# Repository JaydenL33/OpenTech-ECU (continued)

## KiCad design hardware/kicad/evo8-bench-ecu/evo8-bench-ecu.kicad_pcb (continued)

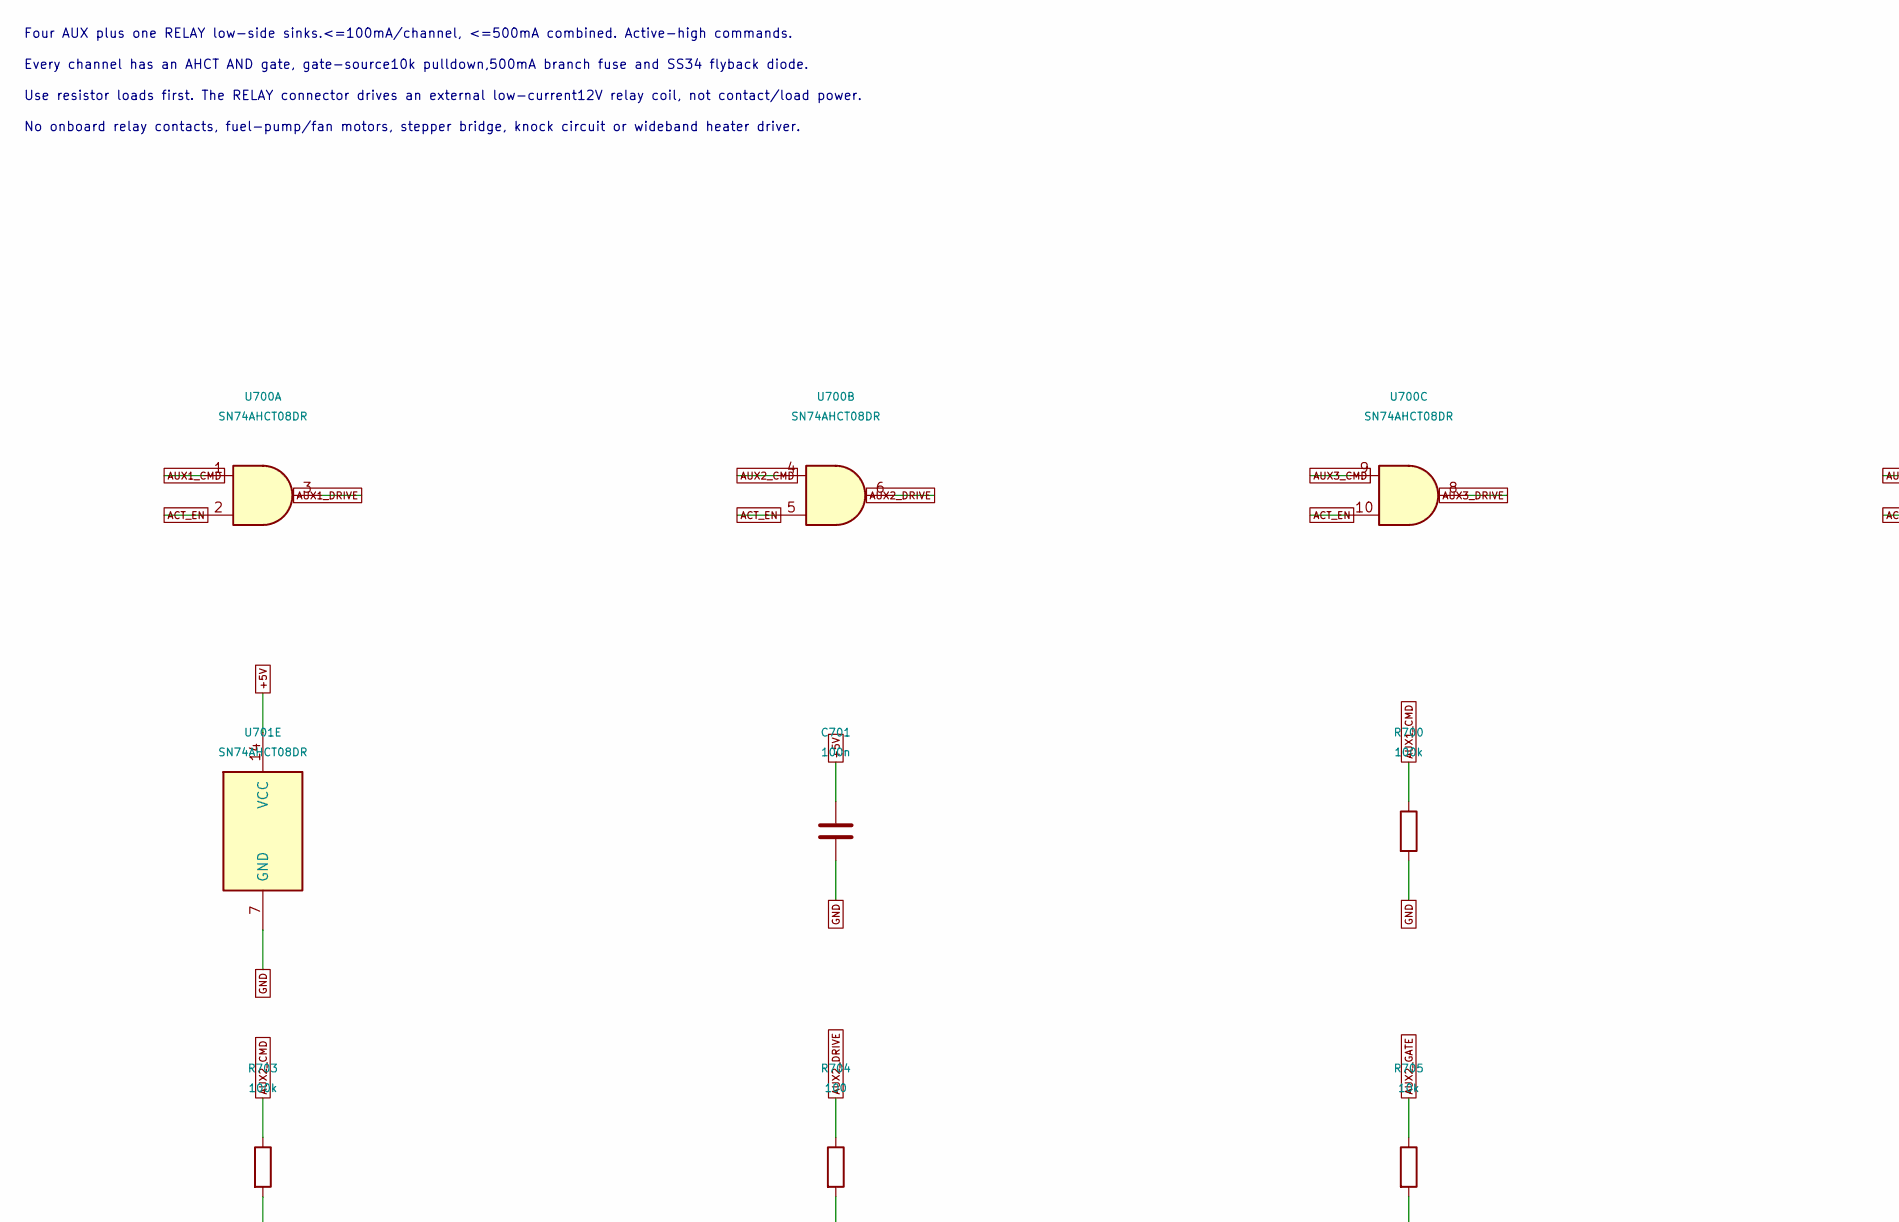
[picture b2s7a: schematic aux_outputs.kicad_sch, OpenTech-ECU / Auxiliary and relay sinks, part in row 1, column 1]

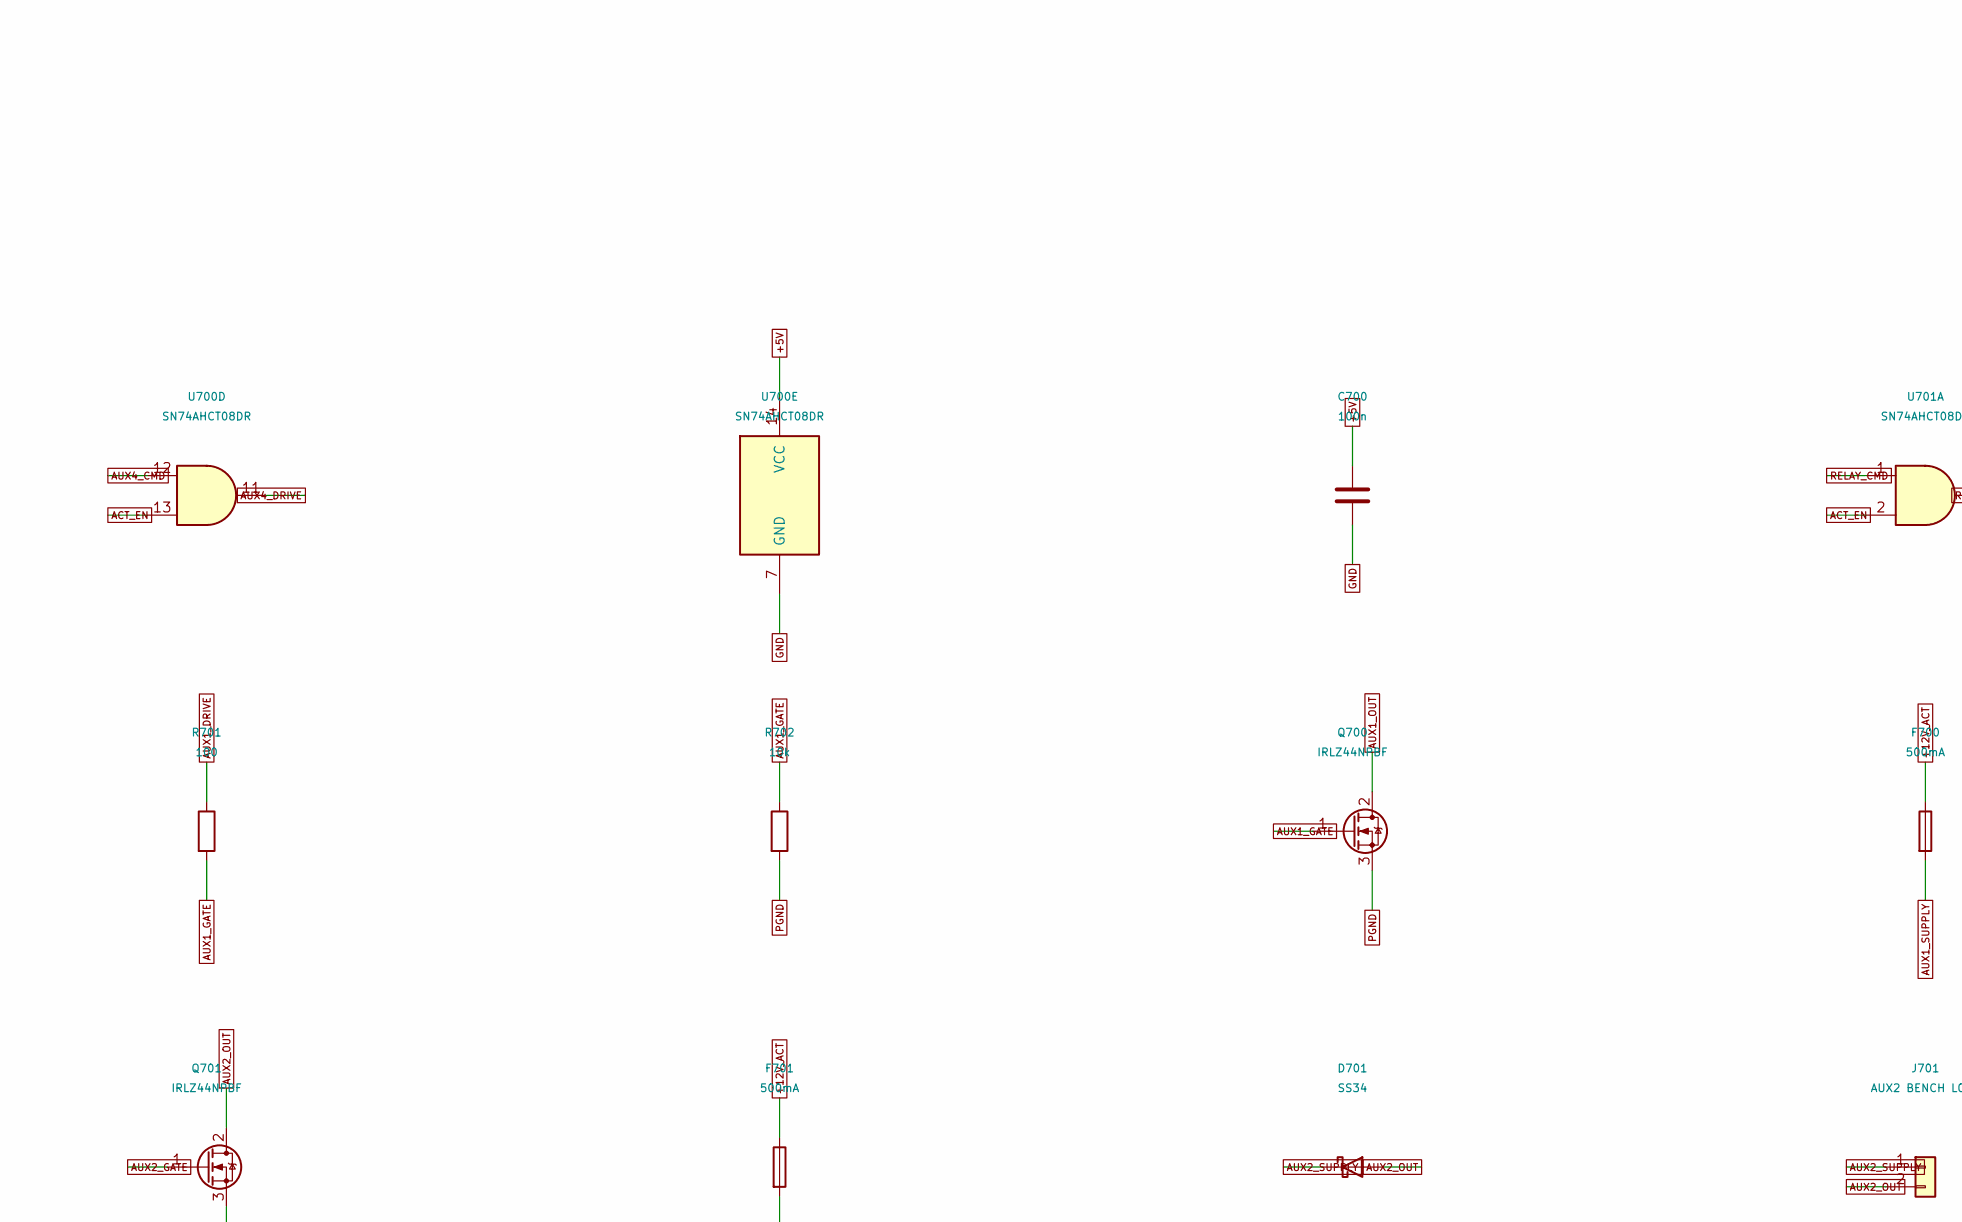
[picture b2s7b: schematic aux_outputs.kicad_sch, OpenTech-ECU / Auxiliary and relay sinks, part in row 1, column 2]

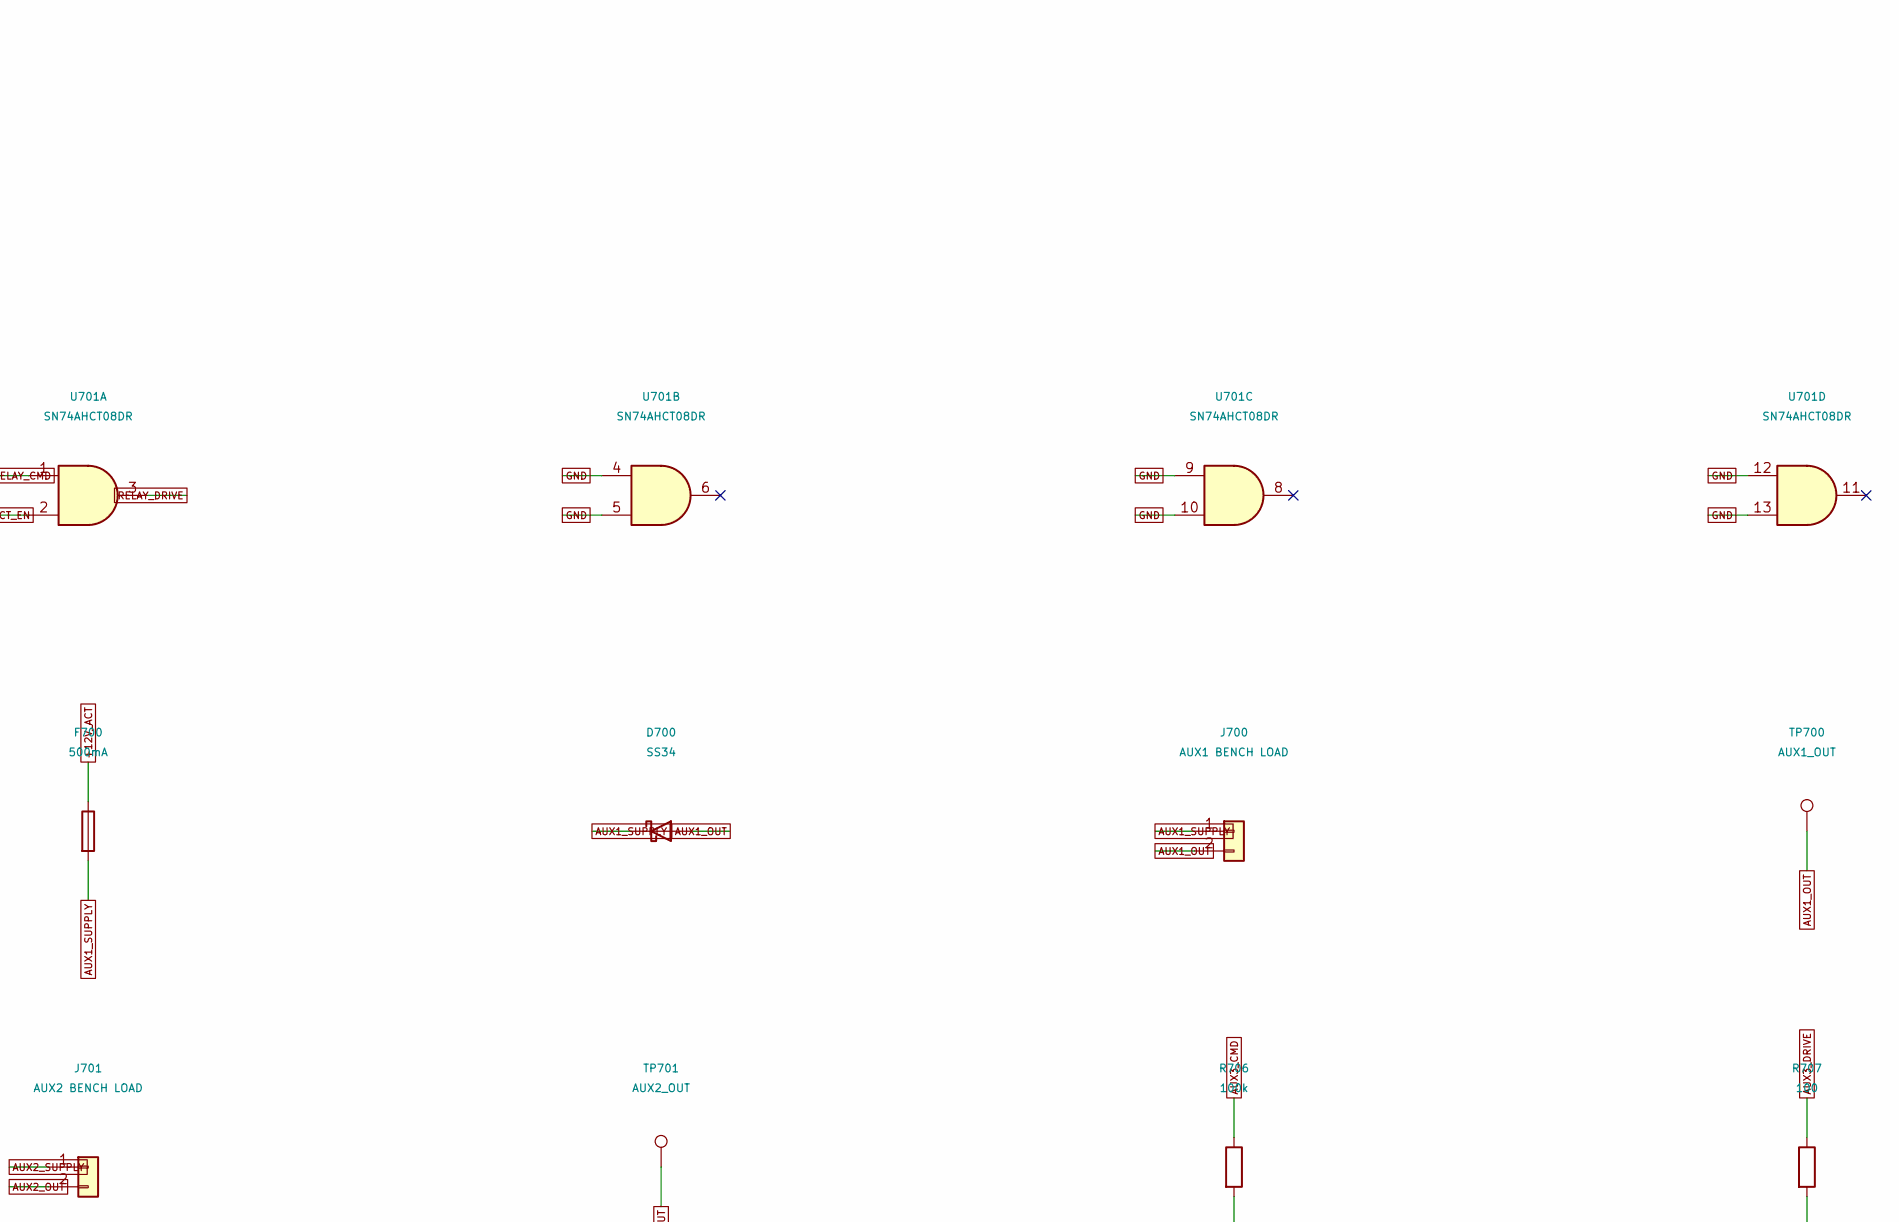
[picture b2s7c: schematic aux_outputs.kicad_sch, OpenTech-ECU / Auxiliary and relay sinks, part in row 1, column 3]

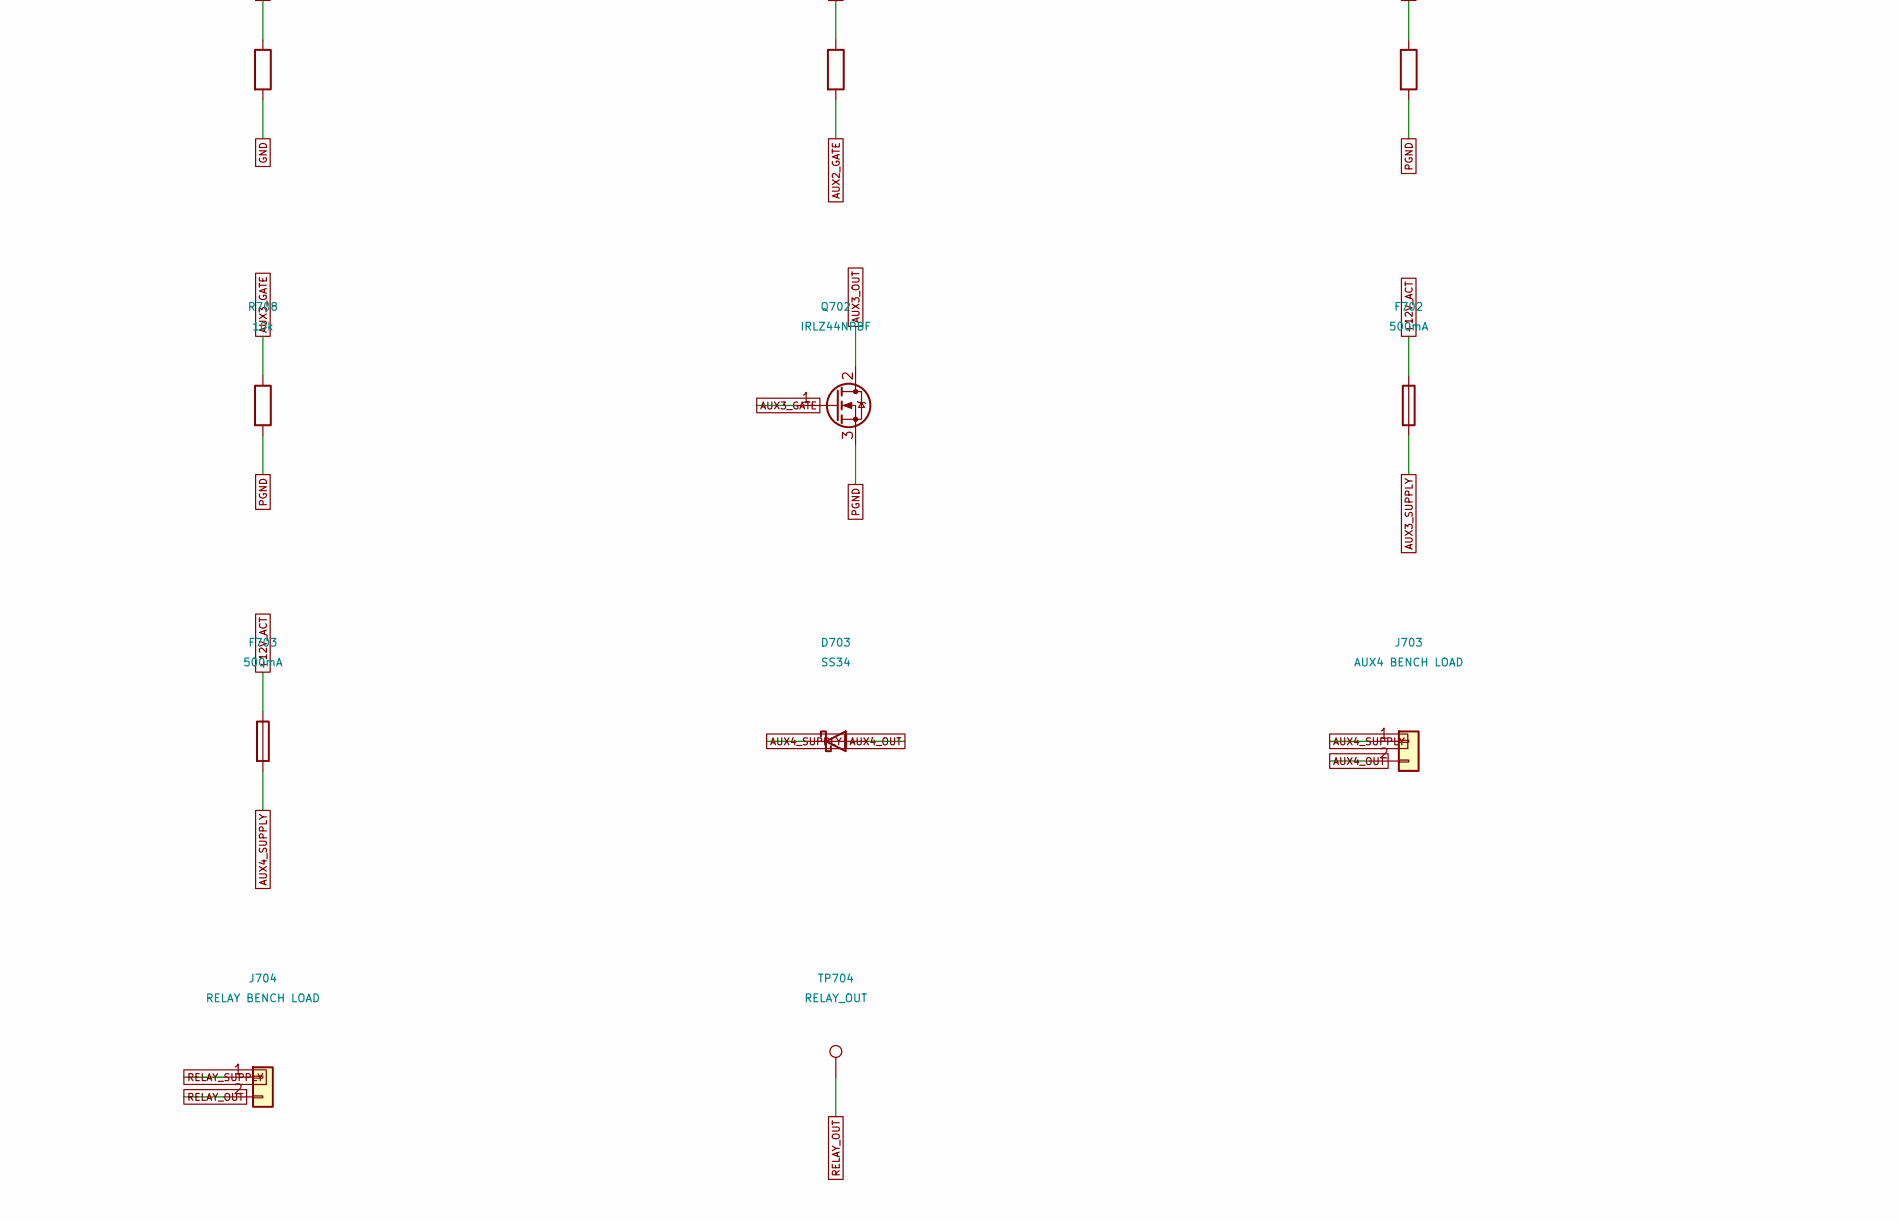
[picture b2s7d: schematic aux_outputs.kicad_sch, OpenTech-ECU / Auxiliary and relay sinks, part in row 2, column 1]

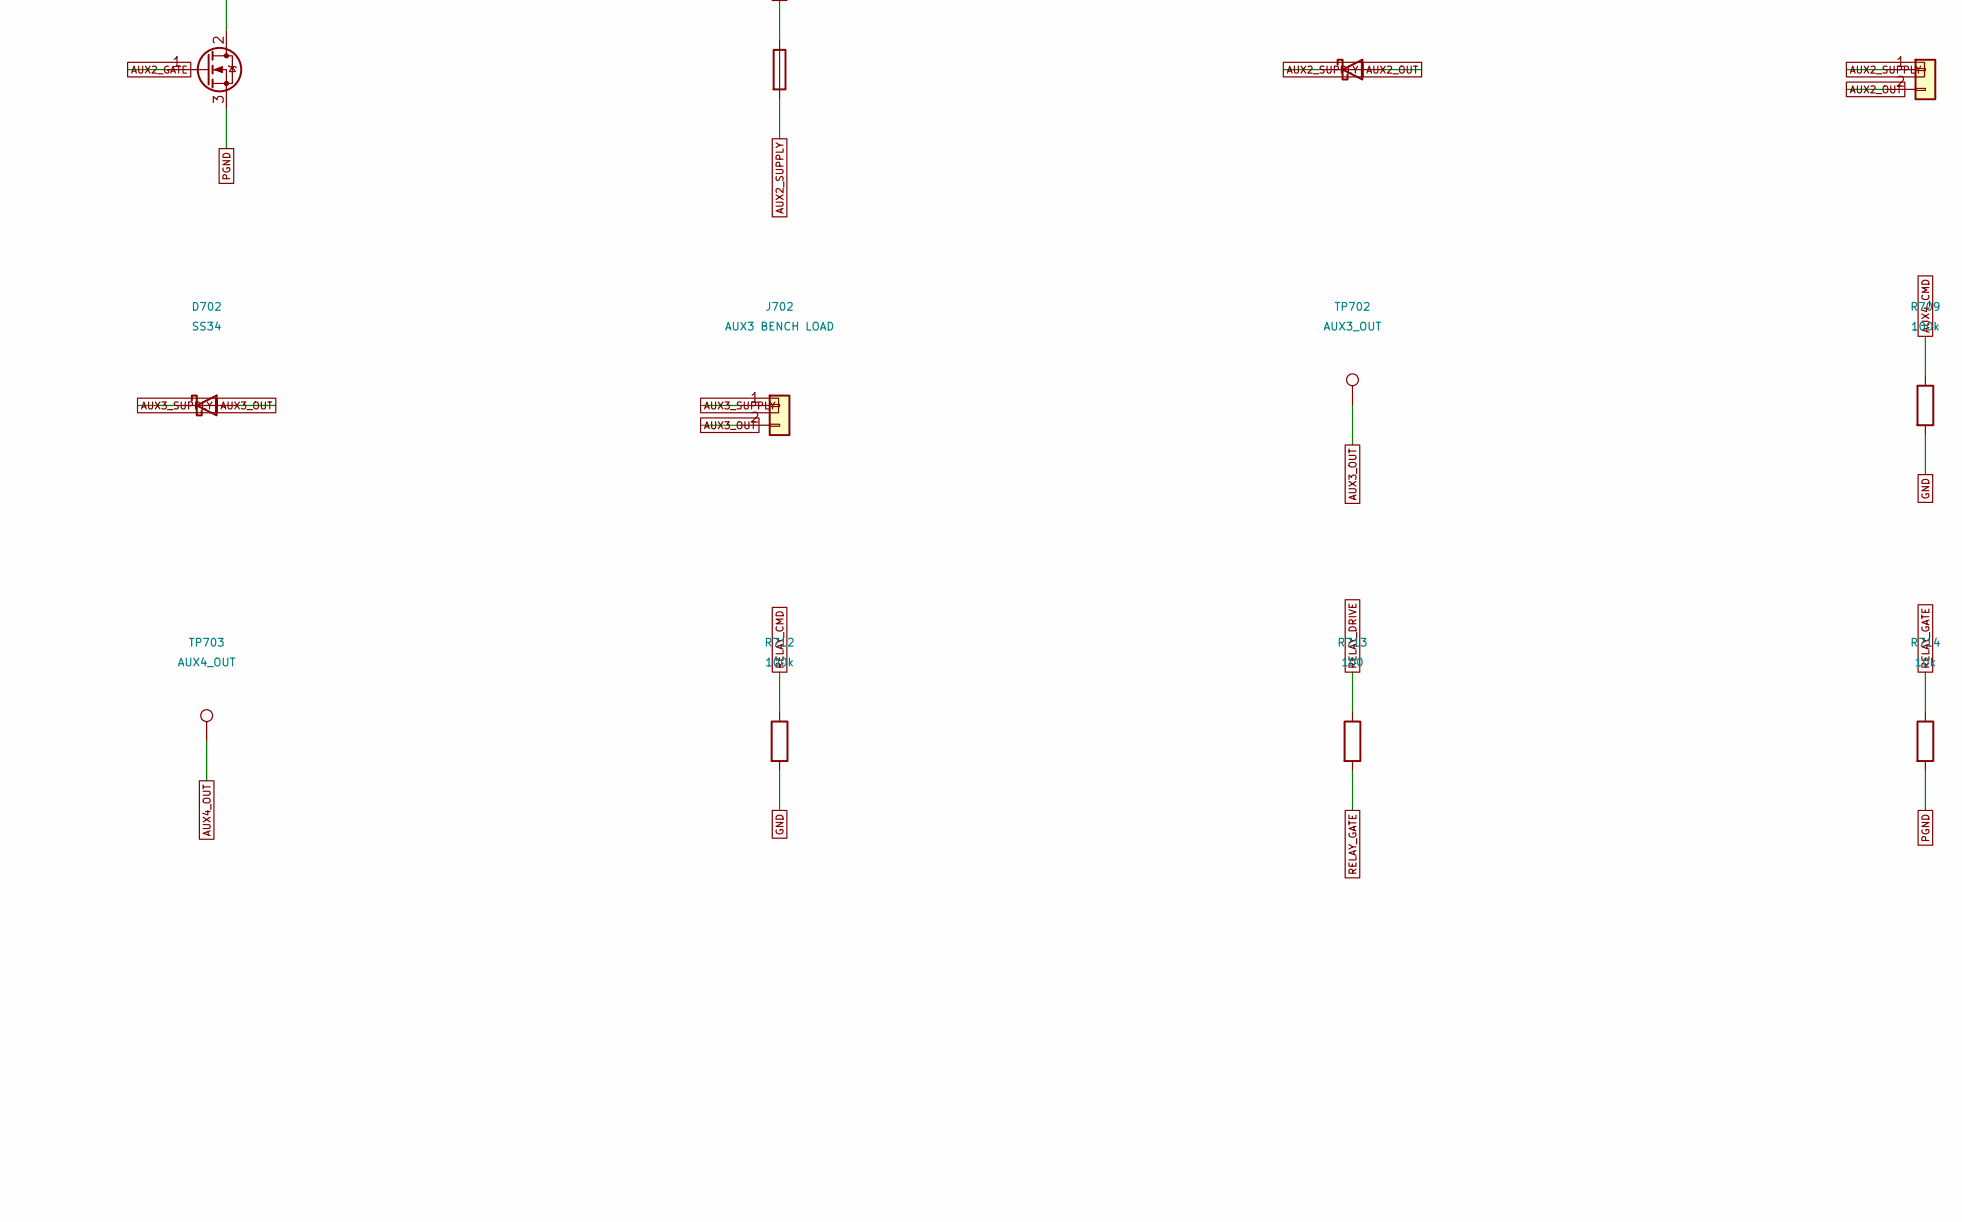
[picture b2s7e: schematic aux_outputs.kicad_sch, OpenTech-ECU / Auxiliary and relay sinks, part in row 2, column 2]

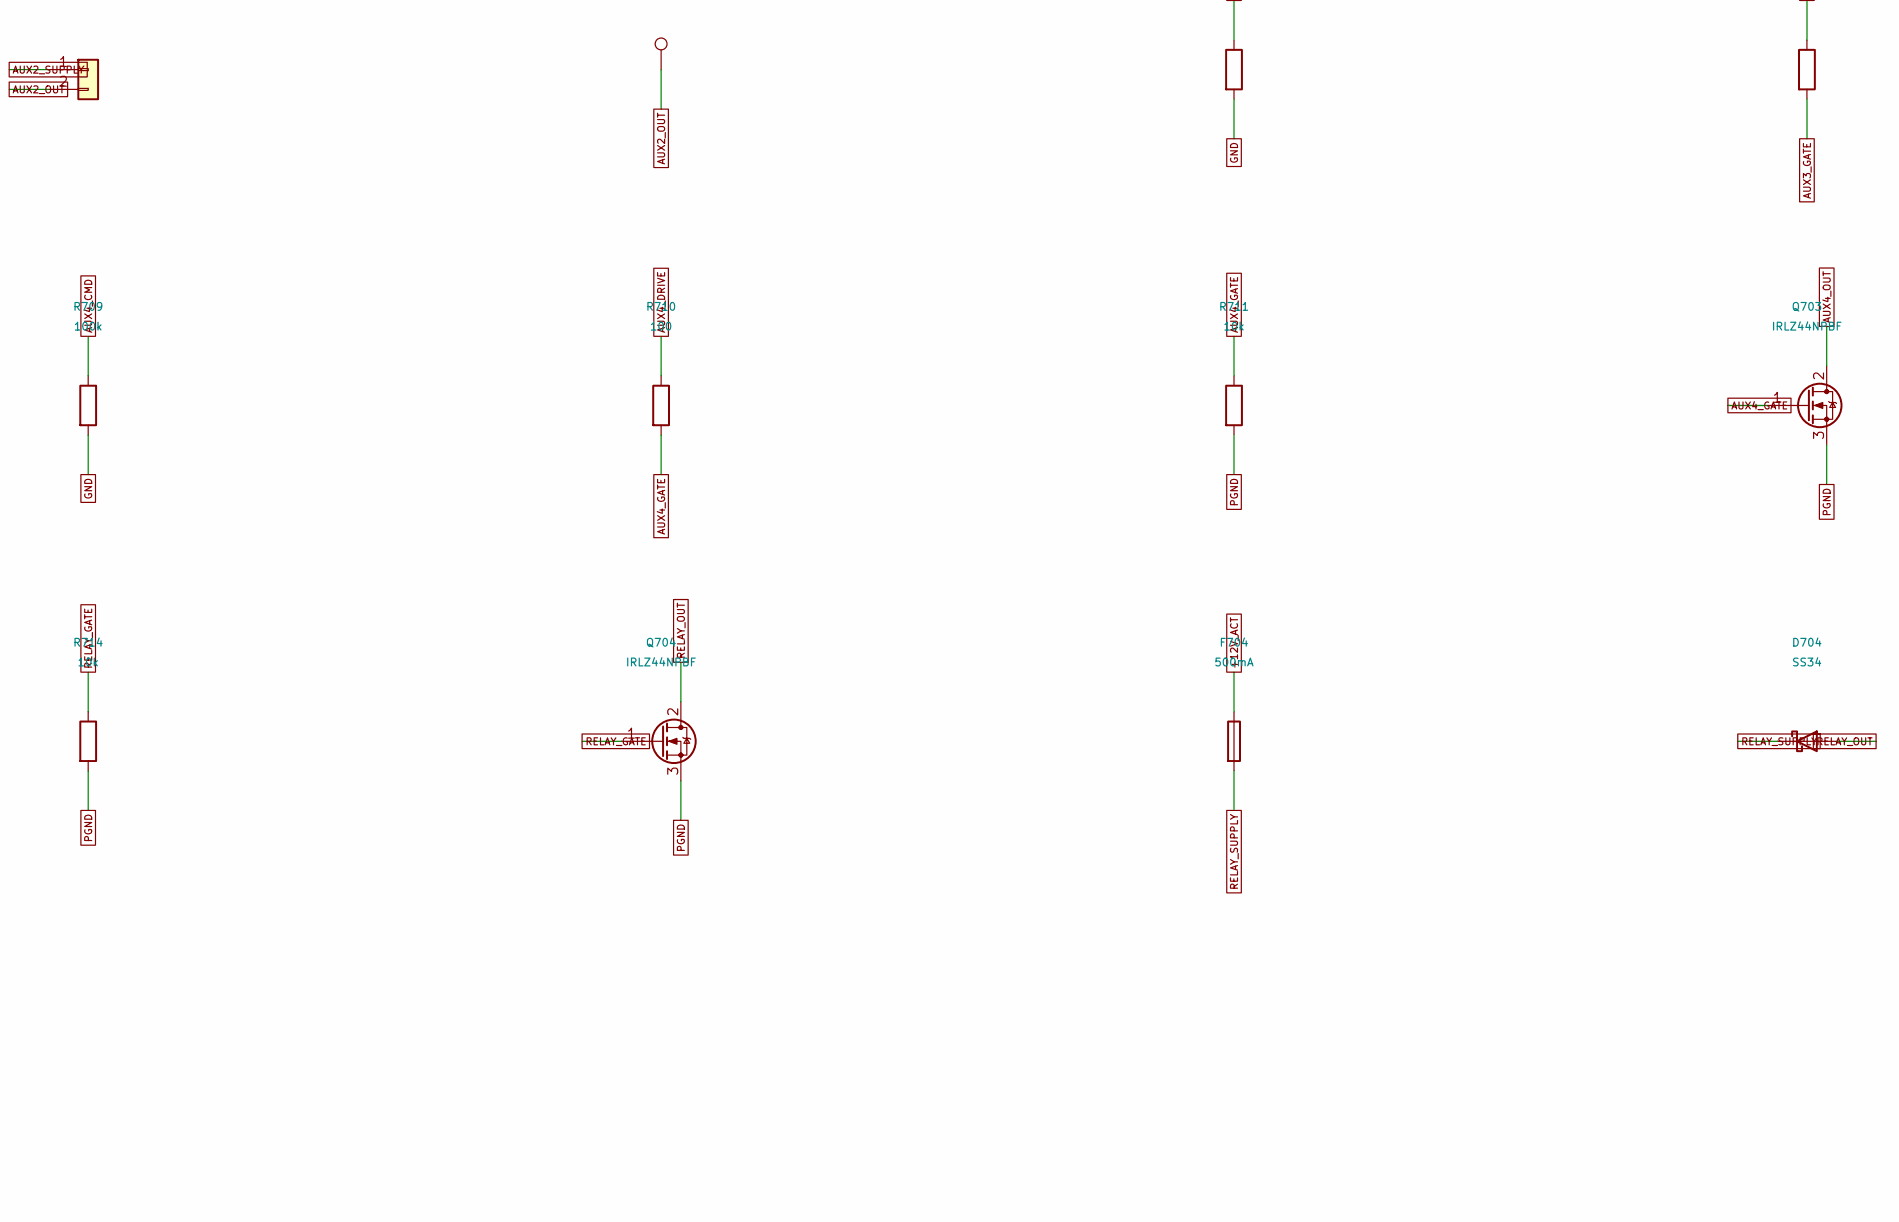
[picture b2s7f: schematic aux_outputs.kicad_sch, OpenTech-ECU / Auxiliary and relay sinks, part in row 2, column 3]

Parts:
C700, C701: 100n; C_0805_2012Metric; MPN GRM21BR71H104KA01L
D700, D701, D702, D703, D704: SS34; D_SMA; MPN SS34
F700, F701, F702, F703, F704: 500mA; Fuse_1206_3216Metric; MPN 0467.500NR
J700: AUX1 BENCH LOAD; TerminalBlock_Phoenix_MKDS-1,5-2-5.08_1x02_P5.08mm_Horizont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; MPN 1715721
J701: AUX2 BENCH LOAD; TerminalBlock_Phoenix_MKDS-1,5-2-5.08_1x02_P5.08mm_Horizont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; MPN 1715721
J702: AUX3 BENCH LOAD; TerminalBlock_Phoenix_MKDS-1,5-2-5.08_1x02_P5.08mm_Horizont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; MPN 1715721
J703: AUX4 BENCH LOAD; TerminalBlock_Phoenix_MKDS-1,5-2-5.08_1x02_P5.08mm_Horizont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; MPN 1715721
J704: RELAY BENCH LOAD; TerminalBlock_Phoenix_MKDS-1,5-2-5.08_1x02_P5.08mm_Horizont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; MPN 1715721
Q700, Q701, Q702, Q703, Q704: IRLZ44NPBF; TO-220-3_Vertical; MPN IRLZ44NPBF
R700, R703, R706, R709, R712: 100k; R_0805_2012Metric; MPN RC0805FR-07100KL
R701, R704, R707, R710, R713: 100; R_0805_2012Metric; MPN RC0805FR-07100RL
R702, R705, R708, R711, R714: 10k; R_0805_2012Metric; MPN RC0805FR-0710KL
TP700: AUX1_OUT; TestPoint_THTPad_D2.0mm_Drill1.0mm; MPN 5010
TP701: AUX2_OUT; TestPoint_THTPad_D2.0mm_Drill1.0mm; MPN 5010
TP702: AUX3_OUT; TestPoint_THTPad_D2.0mm_Drill1.0mm; MPN 5010
TP703: AUX4_OUT; TestPoint_THTPad_D2.0mm_Drill1.0mm; MPN 5010
TP704: RELAY_OUT; TestPoint_THTPad_D2.0mm_Drill1.0mm; MPN 5010
U700, U701: SN74AHCT08DR; SOIC-14_3.9x8.7mm_P1.27mm; MPN SN74AHCT08DR

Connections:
+5V: C700.1, C701.1, U700.14 (VCC), U701.14 (VCC); also elsewhere on the board
+12V_ACT: F700.1, F701.1, F702.1, F703.1, F704.1; also elsewhere on the board
ACT_EN: U700.2, U700.5, U700.10, U700.13, U701.2; also elsewhere on the board
AUX1_CMD: R700.1, U700.1; also elsewhere on the board
AUX1_DRIVE: R701.1, U700.3
AUX1_GATE: Q700.1 (G), R701.2, R702.1
AUX1_OUT: D700.2 (A), J700.2, Q700.2 (D), TP700.1
AUX1_SUPPLY: D700.1 (K), F700.2, J700.1
AUX2_CMD: R703.1, U700.4; also elsewhere on the board
AUX2_DRIVE: R704.1, U700.6
AUX2_GATE: Q701.1 (G), R704.2, R705.1
AUX2_OUT: D701.2 (A), J701.2, Q701.2 (D), TP701.1
AUX2_SUPPLY: D701.1 (K), F701.2, J701.1
AUX3_CMD: R706.1, U700.9; also elsewhere on the board
AUX3_DRIVE: R707.1, U700.8
AUX3_GATE: Q702.1 (G), R707.2, R708.1
AUX3_OUT: D702.2 (A), J702.2, Q702.2 (D), TP702.1
AUX3_SUPPLY: D702.1 (K), F702.2, J702.1
AUX4_CMD: R709.1, U700.12; also elsewhere on the board
AUX4_DRIVE: R710.1, U700.11
AUX4_GATE: Q703.1 (G), R710.2, R711.1
AUX4_OUT: D703.2 (A), J703.2, Q703.2 (D), TP703.1
AUX4_SUPPLY: D703.1 (K), F703.2, J703.1
GND: C700.2, C701.2, R700.2, R703.2, R706.2, R709.2, R712.2, U700.7 (GND), U701.4, U701.5, U701.7 (GND), U701.9, U701.10, U701.12, U701.13; also elsewhere on the board
PGND: Q700.3 (S), Q701.3 (S), Q702.3 (S), Q703.3 (S), Q704.3 (S), R702.2, R705.2, R708.2, R711.2, R714.2; also elsewhere on the board
RELAY_CMD: R712.1, U701.1; also elsewhere on the board
RELAY_DRIVE: R713.1, U701.3
RELAY_GATE: Q704.1 (G), R713.2, R714.1
RELAY_OUT: D704.2 (A), J704.2, Q704.2 (D), TP704.1
RELAY_SUPPLY: D704.1 (K), F704.2, J704.1

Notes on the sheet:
Four AUX plus one RELAY low-side sinks.<=100mA/channel, <=500mA combined. Active-high commands.
Every channel has an AHCT AND gate, gate-source10k pulldown,500mA branch fuse and SS34 flyback diode.
Use resistor loads first. The RELAY connector drives an external low-current12V relay coil, not contact/load power.
No onboard relay contacts, fuel-pump/fan motors, stepper bridge, knock circuit or wideband heater driver.

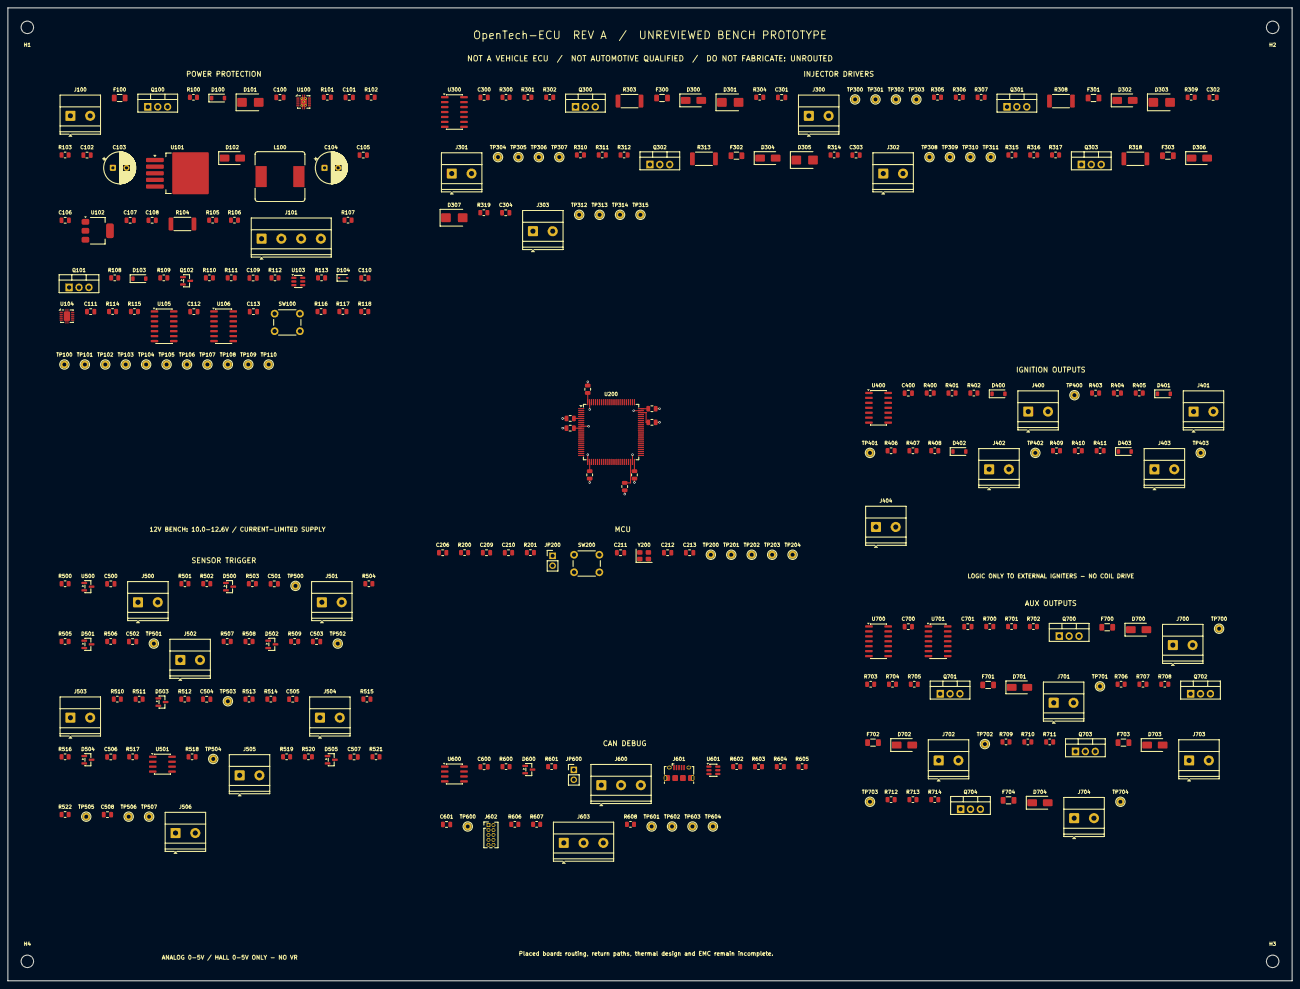
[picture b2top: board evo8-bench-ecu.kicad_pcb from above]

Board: 4 copper layers, 330.0 x 250.0 mm, 305 parts (0 on the bottom side), 137 nets.

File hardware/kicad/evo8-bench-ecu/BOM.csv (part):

Reference,Quantity,Value,Manufacturer,MPN,Footprint,Sheet,Assembly,Design note
J100,1,J_PWR 12V BENCH ONLY,Phoenix Contact,1715721,"TerminalBlock_Phoenix:TerminalBlock_Phoenix_MKDS-1,5-2-5.08_1x02_P5.08mm_Horizontal",power_protection,FIT,Board-local bench connector; pin numbers are NOT OEM cavities
F100,1,2A,Littelfuse,0467002.NR,Fuse:Fuse_1206_3216Metric,power_protection,FIT,Fast fuse; verify interrupt rating and coordination
Q100,1,IRF4905PBF,Infineon,IRF4905PBF,Package_TO_SOT_THT:TO-220-3_Vertical,power_protection,FIT,Reverse protection: D=input S=protected; not ideal-diode backfeed blocking
R100,1,100k,Yageo,RC0805FR-07100KL,Resistor_SMD:R_0805_2012Metric,power_protection,FIT,
D100,1,BZT52C12,Littelfuse,BZT52C12-7-F,Diode_SMD:D_SOD-123,power_protection,FIT,12V gate-source clamp
D101,1,SMBJ12A,Littelfuse,SMBJ12A,Diode_SMD:D_SMB,power_protection,FIT,Bench transient clamp only; no load-dump qualification
C100,1,100n,Murata,GRM21BR71H104KA01L,Capacitor_SMD:C_0805_2012Metric,power_protection,FIT,
U100,1,TPS259260DRCR,Texas Instruments,TPS259260DRCR,Package_SON:VSON-10-1EP_3x3mm_P0.5mm_EP1.65x2.4mm_ThermalVias,power_protection,FIT,"12V variant, latched thermal shutdown; nominal 2.1A limit"
R101,1,45.3k,Yageo,RC0805FR-0745K3L,Resistor_SMD:R_0805_2012Metric,power_protection,FIT,
C101,1,1n,Murata,GRM21B5C1H102JA01L,Capacitor_SMD:C_0805_2012Metric,power_protection,FIT,
R102,1,47k,Yageo,RC0805FR-0747KL,Resistor_SMD:R_0805_2012Metric,power_protection,FIT,
R103,1,10k,Yageo,RC0805FR-0710KL,Resistor_SMD:R_0805_2012Metric,power_protection,FIT,
C102,1,1u,Murata,GRM21BR71H105KA12L,Capacitor_SMD:C_0805_2012Metric,power_protection,FIT,
C103,1,220u 35V,Nichicon,UHE1V221MPD,Capacitor_THT:CP_Radial_D8.0mm_P3.50mm,power_protection,FIT,Input ripple/temperature review required
U101,1,LM2596S-5.0/NOPB,Texas Instruments,LM2596S-5.0/NOPB,Package_TO_SOT_SMD:TO-263-5_TabPin3,power_protection,FIT,
D102,1,SS34,Vishay,SS34,Diode_SMD:D_SMA,power_protection,FIT,
L100,1,33uH,Bourns,SRR1260-330M,Inductor_SMD:L_Bourns_SRR1260,power_protection,FIT,Check saturation and ripple at bench load
C104,1,330u 25V,Nichicon,UHE1E331MPD,Capacitor_THT:CP_Radial_D8.0mm_P3.50mm,power_protection,FIT,Buck stability/ESR requires scope validation
C105,1,100n,Murata,GRM21BR71H104KA01L,Capacitor_SMD:C_0805_2012Metric,power_protection,FIT,
C106,1,10u,Murata,GRM21BR61A106KE19L,Capacitor_SMD:C_0805_2012Metric,power_protection,FIT,
U102,1,LD1117S33TR,STMicroelectronics,LD1117S33TR,Package_TO_SOT_SMD:SOT-223-3_TabPin2,power_protection,FIT,Budget <=350mA; thermal copper still incomplete
C107,1,10u,Murata,GRM21BR61A106KE19L,Capacitor_SMD:C_0805_2012Metric,power_protection,FIT,
C108,1,100n,Murata,GRM21BR71H104KA01L,Capacitor_SMD:C_0805_2012Metric,power_protection,FIT,
R104,1,0,Yageo,RC2512JK-070RL,Resistor_SMD:R_2512_6332Metric,power_protection,FIT,Single logic/power return star; never route injector current through it
R105,1,0,Yageo,RC0805FR-070RL,Resistor_SMD:R_0805_2012Metric,power_protection,FIT,Analog star beside MCU VSSA; no actuator return
R106,1,1k,Yageo,RC0805FR-071KL,Resistor_SMD:R_0805_2012Metric,power_protection,FIT,
J101,1,J_ESTOP EXTERNAL NC CONTACTS,Phoenix Contact,1715747,"TerminalBlock_Phoenix:TerminalBlock_Phoenix_MKDS-1,5-4-5.08_1x04_P5.08mm_Horizontal",power_protection,FIT,Board-local bench connector; pin numbers are NOT OEM cavities
R107,1,100k,Yageo,RC0805FR-07100KL,Resistor_SMD:R_0805_2012Metric,power_protection,FIT,
Q101,1,IRF4905PBF,Infineon,IRF4905PBF,Package_TO_SOT_THT:TO-220-3_Vertical,power_protection,FIT,Actuator high-side switch; NC E-stop precedes source
R108,1,100k,Yageo,RC0805FR-07100KL,Resistor_SMD:R_0805_2012Metric,power_protection,FIT,
D103,1,BZT52C12,Littelfuse,BZT52C12-7-F,Diode_SMD:D_SOD-123,power_protection,FIT,
R109,1,10k,Yageo,RC0805FR-0710KL,Resistor_SMD:R_0805_2012Metric,power_protection,FIT,
Q102,1,MMBT3904LT1G,onsemi,MMBT3904LT1G,Package_TO_SOT_SMD:SOT-23,power_protection,FIT,
R110,1,4.7k,Yageo,RC0805FR-074K7L,Resistor_SMD:R_0805_2012Metric,power_protection,FIT,
R111,1,100k,Yageo,RC0805FR-07100KL,Resistor_SMD:R_0805_2012Metric,power_protection,FIT,
C109,1,1u,Murata,GRM21BR71H105KA12L,Capacitor_SMD:C_0805_2012Metric,power_protection,FIT,
R112,1,1k,Yageo,RC0805FR-071KL,Resistor_SMD:R_0805_2012Metric,power_protection,FIT,Actuator rail discharge; 0.16W at12.6V
U103,1,TPS3808G33DBVR,Texas Instruments,TPS3808G33DBVR,Package_TO_SOT_SMD:SOT-23-6,power_protection,FIT,3.07V threshold; CT open gives20ms nominal reset release
R113,1,10k,Yageo,RC0805FR-0710KL,Resistor_SMD:R_0805_2012Metric,power_protection,FIT,
D104,1,BAT54WS,Diodes Incorporated,BAT54WS-7-F,Diode_SMD:D_SOD-323,power_protection,FIT,"Reset isolation: anode NRST, cathode supervisor; verify low level after diode drop"
C110,1,100n,Murata,GRM21BR71H104KA01L,Capacitor_SMD:C_0805_2012Metric,power_protection,FIT,
U104,1,TPS3430WDRCR,Texas Instruments,TPS3430WDRCR,Package_SON:VSON-10-1EP_3x3mm_P0.5mm_EP1.65x2.4mm,power_protection,FIT,CWD/CRST open; SET0=SET1=0; service falling edge every35ms
C111,1,100n,Murata,GRM21BR71H104KA01L,Capacitor_SMD:C_0805_2012Metric,power_protection,FIT,
R114,1,100k,Yageo,RC0805FR-07100KL,Resistor_SMD:R_0805_2012Metric,power_protection,FIT,
R115,1,10k,Yageo,RC0805FR-0710KL,Resistor_SMD:R_0805_2012Metric,power_protection,FIT,
U105,1,SN74HC08DR,Texas Instruments,SN74HC08DR,Package_SO:SOIC-14_3.9x8.7mm_P1.27mm,power_protection,FIT,Standard quad AND pinout; fit the specified logic family
C112,1,100n,Murata,GRM21BR71H104KA01L,Capacitor_SMD:C_0805_2012Metric,power_protection,FIT,Local bypass for U105
U106,1,SN74HC74DR,Texas Instruments,SN74HC74DR,Package_SO:SOIC-14_3.9x8.7mm_P1.27mm,power_protection,FIT,
C113,1,100n,Murata,GRM21BR71H104KA01L,Capacitor_SMD:C_0805_2012Metric,power_protection,FIT,
SW100,1,ARM BENCH,Omron,B3F-1000,Button_Switch_THT:SW_PUSH_6mm,power_protection,FIT,Press after valid watchdog service; contact bounce cannot defeat asynchronous clear
R116,1,100k,Yageo,RC0805FR-07100KL,Resistor_SMD:R_0805_2012Metric,power_protection,FIT,
R117,1,100k,Yageo,RC0805FR-07100KL,Resistor_SMD:R_0805_2012Metric,power_protection,FIT,
R118,1,100k,Yageo,RC0805FR-07100KL,Resistor_SMD:R_0805_2012Metric,power_protection,FIT,
TP100,1,VIN_BENCH,Keystone,5010,TestPoint:TestPoint_THTPad_D2.0mm_Drill1.0mm,power_protection,FIT,Measure VIN_BENCH relative to GND
TP101,1,+12V_PROTECTED,Keystone,5010,TestPoint:TestPoint_THTPad_D2.0mm_Drill1.0mm,power_protection,FIT,Measure +12V_PROTECTED relative to GND
TP102,1,+12V_ACT,Keystone,5010,TestPoint:TestPoint_THTPad_D2.0mm_Drill1.0mm,power_protection,FIT,Measure +12V_ACT relative to GND
TP103,1,+5V,Keystone,5010,TestPoint:TestPoint_THTPad_D2.0mm_Drill1.0mm,power_protection,FIT,Measure +5V relative to GND
TP104,1,+3V3,Keystone,5010,TestPoint:TestPoint_THTPad_D2.0mm_Drill1.0mm,power_protection,FIT,Measure +3V3 relative to GND
TP105,1,NRST,Keystone,5010,TestPoint:TestPoint_THTPad_D2.0mm_Drill1.0mm,power_protection,FIT,Measure NRST relative to GND
TP106,1,ARMED,Keystone,5010,TestPoint:TestPoint_THTPad_D2.0mm_Drill1.0mm,power_protection,FIT,Measure ARMED relative to GND
TP107,1,ACT_EN,Keystone,5010,TestPoint:TestPoint_THTPad_D2.0mm_Drill1.0mm,power_protection,FIT,Measure ACT_EN relative to GND
TP108,1,PGND,Keystone,5010,TestPoint:TestPoint_THTPad_D2.0mm_Drill1.0mm,power_protection,FIT,Measure PGND relative to GND
TP109,1,GND,Keystone,5010,TestPoint:TestPoint_THTPad_D2.0mm_Drill1.0mm,power_protection,FIT,Measure GND relative to GND
TP110,1,ESTOP_OK,Keystone,5010,TestPoint:TestPoint_THTPad_D2.0mm_Drill1.0mm,power_protection,FIT,Measure ESTOP_OK relative to GND
U200,1,STM32H743VIT6,STMicroelectronics,STM32H743VIT6,Package_QFP:LQFP-100_14x14mm_P0.5mm,mcu,FIT,
C200,1,100n,Murata,GRM21BR71H104KA01L,Capacitor_SMD:C_0805_2012Metric,mcu,FIT,Place beside U200 VDD pin11
C201,1,100n,Murata,GRM21BR71H104KA01L,Capacitor_SMD:C_0805_2012Metric,mcu,FIT,Place beside U200 VDD pin27
C202,1,100n,Murata,GRM21BR71H104KA01L,Capacitor_SMD:C_0805_2012Metric,mcu,FIT,Place beside U200 VDD pin50
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
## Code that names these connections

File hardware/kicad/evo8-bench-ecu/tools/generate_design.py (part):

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      'PWR_FLAG marks intended source nets for ERC; it does not verify voltage, current, or safe operation.']

MCU_MAP={
 'PA0':('CRANK_DIG','TIM2_CH1 AF1 input capture'), 'PA1':('CAM_DIG','TIM2_CH2 AF1 input capture'),
 'PA2':('UART_TX','USART2_TX AF7'), 'PA3':('UART_RX','USART2_RX AF7'),
 'PA4':('ADC_AN1','ADC12_INP18'), 'PA5':('ADC_AN2','ADC12_INP19'),
 'PA6':('ADC_AN3','ADC12_INP3'), 'PA7':('ADC_AN4','ADC12_INP7'),
 'PA9':('USB_VBUS_SENSE','GPIO VBUS sense; see USB firmware requirements'),
 'PA11':('USB_DM','USB_OTG_FS_DM AF10'), 'PA12':('USB_DP','USB_OTG_FS_DP AF10'),
 'PA13':('SWDIO','SWD AF0'), 'PA14':('SWCLK','SWD AF0'), 'PB3':('SWO','TRACE_SWO AF0'),
 'PB8':('CAN_RX','FDCAN1_RX AF9, classic CAN only'), 'PB9':('CAN_TX','FDCAN1_TX AF9'),
 'PE9':('INJ1_CMD','TIM1_CH1 AF1'), 'PE11':('INJ2_CMD','TIM1_CH2 AF1'),
 'PE13':('INJ3_CMD','TIM1_CH3 AF1'), 'PE14':('INJ4_CMD','TIM1_CH4 AF1'),
 'PD12':('IGN1_CMD','TIM4_CH1 AF2'), 'PD13':('IGN2_CMD','TIM4_CH2 AF2'),
 'PD14':('IGN3_CMD','TIM4_CH3 AF2'), 'PD15':('IGN4_CMD','TIM4_CH4 AF2'),
 'PC6':('AUX1_CMD','TIM3_CH1 AF2'), 'PC7':('AUX2_CMD','TIM3_CH2 AF2'),
 'PC8':('AUX3_CMD','TIM3_CH3 AF2'), 'PC9':('AUX4_CMD','TIM3_CH4 AF2'),
 'PB0':('RELAY_CMD','GPIO push-pull active high'), 'PB1':('MCU_ENABLE','GPIO active high; firmware must default low'),
 'PB2':('WD_KICK','GPIO software falling edge heartbeat; do not use autonomous PWM'),
 'PC0':('ADC_IS1','ADC123_INP10'), 'PC1':('ADC_IS2','ADC123_INP11'),
 'PC4':('ADC_IS3','ADC12_INP4'), 'PC5':('ADC_IS4','ADC12_INP8'),
 'PC13':('ARMED','GPIO latch state input'), 'PD2':('ESTOP_OK','GPIO E-stop state input')}
def make_mcu():
    s='mcu';sym=symbol('MCU_ST_STM32H7:STM32H743VITx');conn={}
    fixed={'NRST':'NRST','BOOT0':'BOOT0','VREF+':'VDDA','PH0':'HSE_IN','PH1':'HSE_OUT',
           'VBAT':'+3V3','VDD':'+3V3','VSS':'GND','VSSA':'AGND','VDDA':'VDDA'}
    for p in pins(sym):
        conn[p['num']]=MCU_MAP[p['name']][0] if p['name'] in MCU_MAP else fixed.get(p['name'])
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    for pin in ['11','27','50','75','100']:
        C(s,'100n','+3V3',note='Place beside U200 VDD pin'+pin)
    C(s,'100n','+3V3',note='VBAT local bypass');C(s,'10u','+3V3',note='MCU bulk')
    C(s,'2.2u','VCAP48',note='U200 pin48 core LDO output; no other load')
    C(s,'2.2u','VCAP73',note='U200 pin73 core LDO output; no other load')
    R(s,'10','+3V3','VDDA',note='Analog rail RC isolator; verify drop at ADC load')
    C(s,'1u','VDDA','AGND');C(s,'100n','VDDA','AGND')
    R(s,'100k','BOOT0','GND')
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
